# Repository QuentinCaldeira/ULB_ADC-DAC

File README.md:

# ULB_ADC-DAC

Ce git contient tout les documents liés à la conception de la carte de protection des calculateurs analogiques ADC/DAC.
Dans ce git, vous pouvez trouver :

## Datasheets

Ce répertoire contient toutes les **datasheets** et **notes d'application** qui ont étés utilisées dans la conception dde ce projet.

## Documentation PCB

Ce répertoire contient tout les fichiers de conception du PCB pour le logiciel KiCAD. Des images de la carte et du schematic ont aussi été mis à disposition.

## Gravure

Ce répertoire contient principalement le fichier `.svg` qui à été utilisé pour graver la face avant de la carte, ainsi qu'un template **à l'échelle** pour le gabarit 8x5.

## LaTeX

Ce répertoire contient tout les fichiers liés à la compilation LaTeX du fichier `Documenation.pdf`. Il y a toutes les images liées au document, le template global, les logos, etc...

## Tuto

Ce répertoire contient des tutoriels écrits en `markdown`. Ces tutoriels ont été écrits lorsque j'ai rencontré des difficultés à faire une tâche.

## 3D

Ce répertoire contient les fichiers 3D FreeCAD et `.stl` pour imprimer les pièces permettant de visser la face avant au PCB.

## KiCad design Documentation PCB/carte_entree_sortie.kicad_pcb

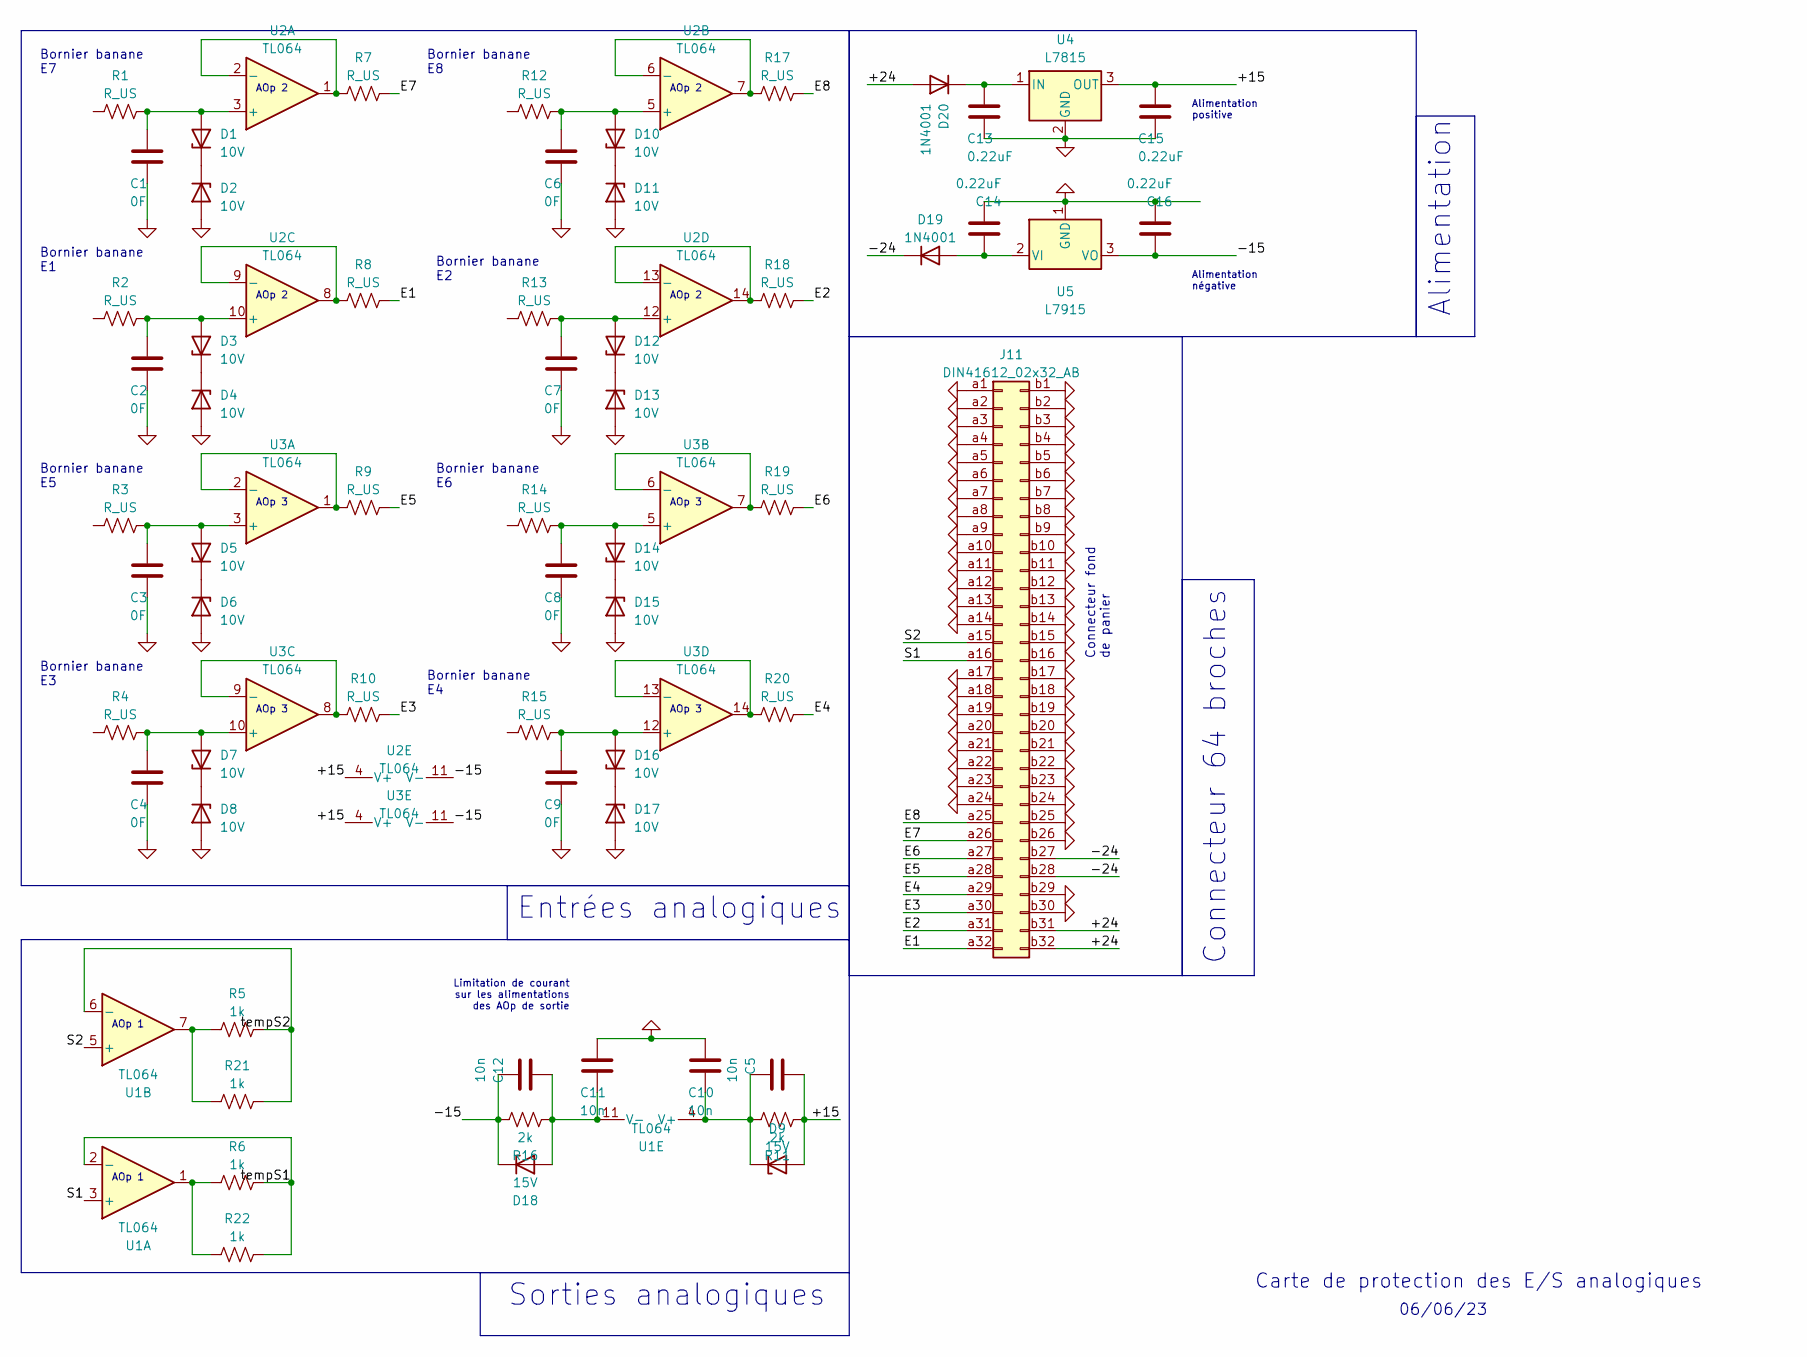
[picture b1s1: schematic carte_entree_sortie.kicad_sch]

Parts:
C1, C2, C3, C4, C6, C7, C8, C9: 0F; C_Axial_L3.8mm_D2.6mm_P7.50mm_Horizontal
C5, C12: 10n; C_Disc_D3.8mm_W2.6mm_P2.50mm
C10, C11: 10n; C_Disc_D4.7mm_W2.5mm_P5.00mm
C13, C14, C15, C16: 0.22uF; C_Rect_L11.0mm_W3.4mm_P10.00mm_MKT
D1, D2, D3, D4, D5, D6, D7, D8, D10, D11, D12, D13, D14, D15, D16, D17: 10V; D_DO-41_SOD81_P7.62mm_Horizontal
D9, D18: 15V; D_DO-41_SOD81_P7.62mm_Horizontal
D19, D20: 1N4001; D_DO-41_SOD81_P10.16mm_Horizontal
J11: DIN41612_02x32_AB; DIN41612_B_2x32_Male_Horizontal_THT
R1, R2, R3, R4, R7, R8, R9, R10, R12, R13, R14, R15, R17, R18, R19, R20: R_US; R_Axial_DIN0207_L6.3mm_D2.5mm_P10.16mm_Horizontal
R5, R6, R21, R22: 1k; R_Axial_DIN0309_L9.0mm_D3.2mm_P20.32mm_Horizontal
R11, R16: 2k; R_Axial_DIN0309_L9.0mm_D3.2mm_P15.24mm_Horizontal
U1, U2, U3: TL064; DIP-14_W7.62mm
U4: L7815; TO-220-3_Vertical
U5: L7915; TO-220-3_Vertical

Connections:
/+15: C5.1, C15.1, D9.2 (A), R11.1, U2.4 (V+), U3.4 (V+), U4.3 (OUT)
/+24: D20.2 (A), J11.b31, J11.b32
/-15: C12.2, C16.1, D18.1 (K), R16.2, U2.11 (V-), U3.11 (V-), U5.3 (VO)
/-24: D19.1 (K), J11.b27, J11.b28
/E1: J11.a32, R8.2
/E2: J11.a31, R18.2
/E3: J11.a30, R10.2
/E4: J11.a29, R20.2
/E5: J11.a28, R9.2
/E6: J11.a27, R19.2
/E7: J11.a26, R7.2
/E8: J11.a25, R17.2
/S1: J11.a16, U1.3 (+)
/S2: J11.a15, U1.5 (+)
/tempS1: R6.2, R22.2, U1.2 (-)
/tempS2: R5.2, R21.2, U1.6 (-)
GND: C1.2, C2.2, C3.2, C4.2, C6.2, C7.2, C8.2, C9.2, C10.1, C11.1, C13.2, C14.2, C15.2, C16.2, D2.2 (A), D4.2 (A), D6.2 (A), D8.2 (A), D11.2 (A), D13.2 (A), D15.2 (A), D17.2 (A), J11.a1, J11.a2, J11.a3, J11.a4, J11.a5, J11.a6, J11.a7, J11.a8, J11.a9, J11.a10, J11.a11, J11.a12, J11.a13, J11.a14, J11.a17, J11.a18, J11.a19, J11.a20, J11.a21, J11.a22, J11.a23, J11.a24, J11.b1, J11.b2, J11.b3, J11.b4, J11.b5, J11.b6, J11.b7, J11.b8, J11.b9, J11.b10, J11.b11, J11.b12, J11.b13, J11.b14, J11.b15, J11.b16, J11.b17, J11.b18, J11.b19, J11.b20, J11.b21, J11.b22, J11.b23, J11.b24, J11.b25, J11.b26, J11.b29, J11.b30, U4.2 (GND), U5.1 (GND)
unnamed: C1.1, D1.2 (A), R1.2, U2.3 (+)
unnamed: D1.1 (K), D2.1 (K)
unnamed: C2.1, D3.2 (A), R2.2, U2.10 (+)
unnamed: D3.1 (K), D4.1 (K)
unnamed: C3.1, D5.2 (A), R3.2, U3.3 (+)
unnamed: D5.1 (K), D6.1 (K)
unnamed: C4.1, D7.2 (A), R4.2, U3.10 (+)
unnamed: D7.1 (K), D8.1 (K)
unnamed: C5.2, C10.2, D9.1 (K), R11.2, U1.4 (V+)
unnamed: C6.1, D10.2 (A), R12.2, U2.5 (+)
unnamed: D10.1 (K), D11.1 (K)
unnamed: C7.1, D12.2 (A), R13.2, U2.12 (+)
unnamed: D12.1 (K), D13.1 (K)
unnamed: C8.1, D14.2 (A), R14.2, U3.5 (+)
unnamed: D14.1 (K), D15.1 (K)
unnamed: C9.1, D16.2 (A), R15.2, U3.12 (+)
unnamed: D16.1 (K), D17.1 (K)
unnamed: C11.2, C12.1, D18.2 (A), R16.1, U1.11 (V-)
unnamed: C14.1, D19.2 (A), U5.2 (VI)
unnamed: C13.1, D20.1 (K), U4.1 (IN)
unnamed: R5.1, R21.1, U1.7
unnamed: R6.1, R22.1, U1.1
unnamed: R7.1, U2.1, U2.2 (-)
unnamed: R17.1, U2.6 (-), U2.7
unnamed: R8.1, U2.8, U2.9 (-)
unnamed: R18.1, U2.13 (-), U2.14
unnamed: R9.1, U3.1, U3.2 (-)
unnamed: R19.1, U3.6 (-), U3.7
unnamed: R10.1, U3.8, U3.9 (-)
unnamed: R20.1, U3.13 (-), U3.14

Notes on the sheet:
06/06/23
Bornier banane E5
Bornier banane E2
AOp 1
AOp 2
AOp 3
Alimentation positive
Bornier banane E4
Bornier banane E7
Bornier banane E6
Bornier banane E1
Bornier banane E8
Entrées analogiques
Alimentation négative
Carte de protection des E/S analogiques
Connecteur 64 broches
Alimentation
Connecteur fond de panier
Bornier banane E3
Limitation de courant sur les alimentations des AOp de sortie
Sorties analogiques

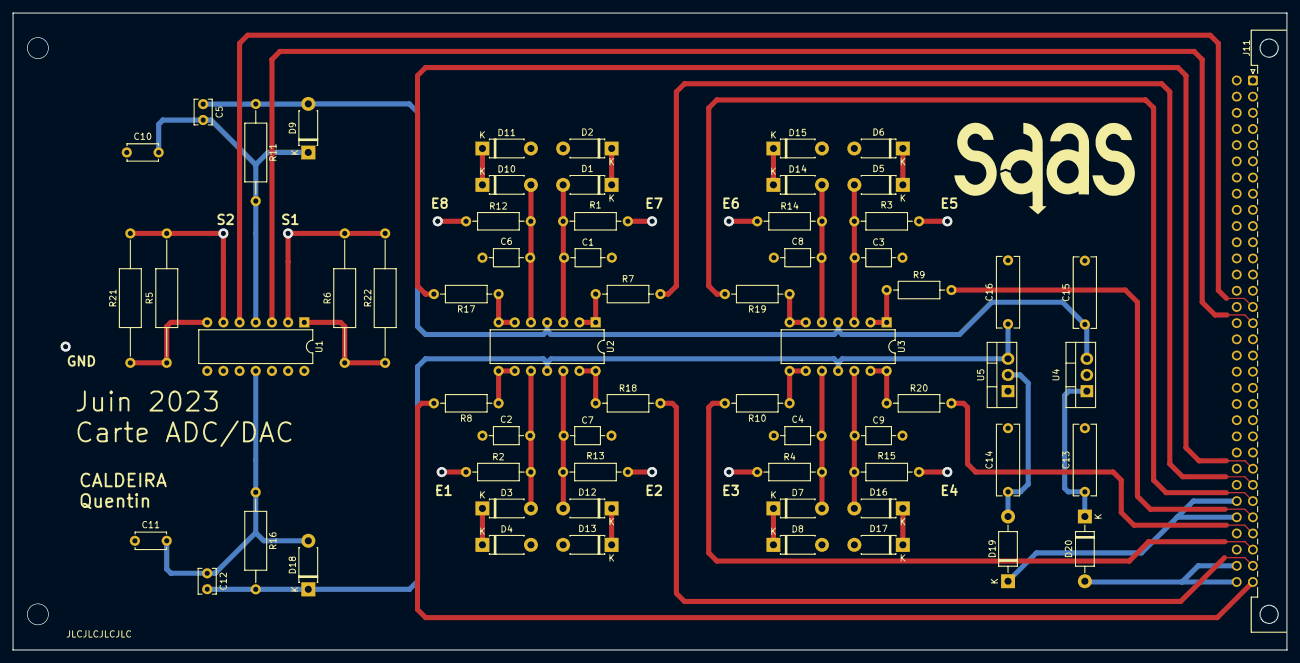
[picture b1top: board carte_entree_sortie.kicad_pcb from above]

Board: 2 copper layers, 200.0 x 100.0 mm, 64 parts (0 on the bottom side), 47 nets.

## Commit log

2023-06-20 Add JLC2KICAD Tutorial
2023-06-20 PDF File for documentation
2023-06-20 Collection of all atasheets for the project
2023-06-20 All files about PCB conception
2023-06-20 All .svg files
2023-06-20 All LaTeX files
    All LaTeX files which are necessary to create the Documentation pdf
2023-06-21 Add NI PCIe documentation
2023-06-21 Update PCB repo with BOM in pdf
2023-06-21 Create tutorial for JLC command
2023-06-21 add inkscape tutorial
2023-06-21 Update documentation pdf file
2023-06-21 add some applications note
2023-07-20 Correct documentation
